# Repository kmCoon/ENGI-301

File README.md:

# ENGI 301
 
<h1>"ENGI301"</h1>
"Repository for ENGI301 course work"

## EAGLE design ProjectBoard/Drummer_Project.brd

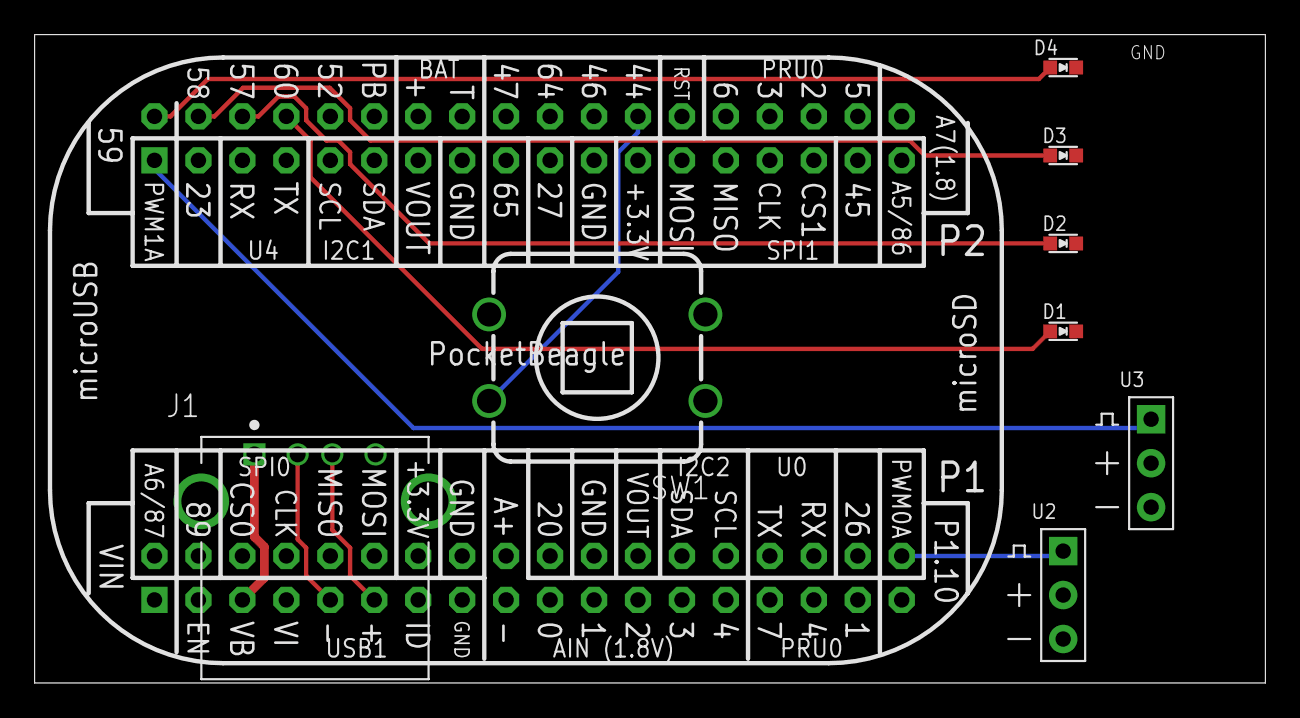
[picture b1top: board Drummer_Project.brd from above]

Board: 2 copper layers, 71.1 x 37.5 mm, 9 parts (0 on the bottom side), 12 nets.

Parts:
D1, D2, D3, D4: LED; EIA-STD
J1: 292303-1; TE_292303-1
SW1: PUSH_BUTTON; BUTTON_12.5MM
U1: POCKETBEAGLE
U2, U3: SERVO_SG90; SERVO-X1

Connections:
GND: D1.CATHODE, D2.CATHODE, D3.CATHODE, D4.CATHODE, J1.4, SW1.2, SW1.4, U1.P1_16, U1.P1_22, U1.P2_15, U1.P2_21, U2.GND, U3.GND
unnamed: SW1.3, U1.P2_24
unnamed: D4.ANODE, U1.P2_02
unnamed: D3.ANODE, U1.P2_04
unnamed: D1.ANODE, U1.P2_08
unnamed: D2.ANODE, U1.P2_06
unnamed: U1.P1_36, U2.SIG
unnamed: U1.P2_01, U3.SIG
unnamed: J1.1, U1.P1_05
unnamed: J1.2, U1.P1_09
unnamed: J1.3, U1.P1_11
VDD_3V3: SW1.1, U1.P1_01, U1.P1_02, U1.P1_07, U1.P1_14, U1.P1_17, U1.P1_18, U1.P1_19, U1.P1_21, U1.P1_23, U1.P1_24, U1.P1_25, U1.P1_27, U1.P2_12, U1.P2_13, U1.P2_14, U1.P2_16, U1.P2_23, U1.P2_26, U1.P2_36, U2.PWR, U3.PWR

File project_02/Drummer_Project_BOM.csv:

"Part";"Value";"Device";"Package";"Description";"AVAILABILITY";"COMMENT";"DESCRIPTION";"EU_ROHS_COMPLIANCE";"MF";"MP";"PACKAGE";"PRICE";"PURCHASE-URL";
"D1";"LED";"LED";"EIA-STD";"EIA-STD LED, LTST-C191TBKT";"";"";"";"";"";"";"";"";"";
"D2";"LED";"LED";"EIA-STD";"EIA-STD LED, LTST-C191TBKT";"";"";"";"";"";"";"";"";"";
"D3";"LED";"LED";"EIA-STD";"EIA-STD LED, LTST-C191TBKT";"";"";"";"";"";"";"";"";"";
"D4";"LED";"LED";"EIA-STD";"EIA-STD LED, LTST-C191TBKT";"";"";"";"";"";"";"";"";"";
"J1";"292303-1";"292303-1";"TE_292303-1";"CONN USB RECEPT R/A TYPE A 4POS Check availability";"In Stock";"292303-1";" Conn";" Data";" USB";" Recept";" 2.0";" 4 Pos";" 1 Port";
"SW1";"PUSH_BUTTON";"PUSH_BUTTON";"BUTTON_12.5MM";"";"";"";"";"";"";"";"";"";"";
"U1";"POCKETBEAGLE";"POCKETBEAGLE";"POCKETBEAGLE";"";"";"";"";"";"";"";"";"";"";
"U2";"SERVO_SG90";"SERVO_SG90";"SERVO-X1";"";"";"";"";"";"";"";"";"";"";
"U3";"SERVO_SG90";"SERVO_SG90";"SERVO-X1";"";"";"";"";"";"";"";"";"";"";

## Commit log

2023-01-26 Added descriptions according to assignment #2.
2023-02-14 Added python
    Added some files :D
2023-02-14 Changes
    yay
2023-02-14 Altered pins in LED code
    Alterations!
2023-02-14 USR3
2023-02-14 Added Button!
2023-02-16 Added project files
2023-02-16 Updated Proposal
2023-02-16 Added software diagramming + pseudocode
2023-02-26 Matlab Add-Ons
    Added Matlab fourier analysis code to the project!
2023-02-28 Added metronome program
    Added main program and made small changes to other functions!
2023-02-28 Hardware test addition
2023-03-05 Proposals and Classes
    Updates!
2023-03-07 Added microphone class + altered software API!
    Added lots of little things
2023-03-22 Revert "Added microphone class + altered software API!"
    This reverts commit 7ff8114d42f2b61b24c9f5bb6a5dc331793f4934.
2023-03-22 Re-Added delete files and updated test code
    yaaay
2023-03-22 yay
    yay
2023-03-22 Microphone updates
    Yay!
2023-03-29 Updates + Added Drumservo/Mic Changes
    yay
2023-04-04 Made some final changes! more 2 come probs
2023-04-04 Updated metronome!
2023-04-28 Added PCB!
    here :)
2023-04-28 Changes!
    here
2023-04-29 Added BOM/Schematics!
    here
2023-04-30 Added BOM/Quotes!
    here
2023-04-30 final update
    :)
